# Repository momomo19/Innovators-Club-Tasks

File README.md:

# Innovators Club Tasks

Work from my sessions with Innovators Club, where we're building an energy-efficient
electric car to race in Shell's International Eco-marathon competition. These are some of the
embedded electronics tasks we worked on that built up the skills that we're now using to develop the car's
actual dashboard and GUI pitwall.

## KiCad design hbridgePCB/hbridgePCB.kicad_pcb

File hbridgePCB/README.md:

A single layer H-Bridge PCB I made from scratch.

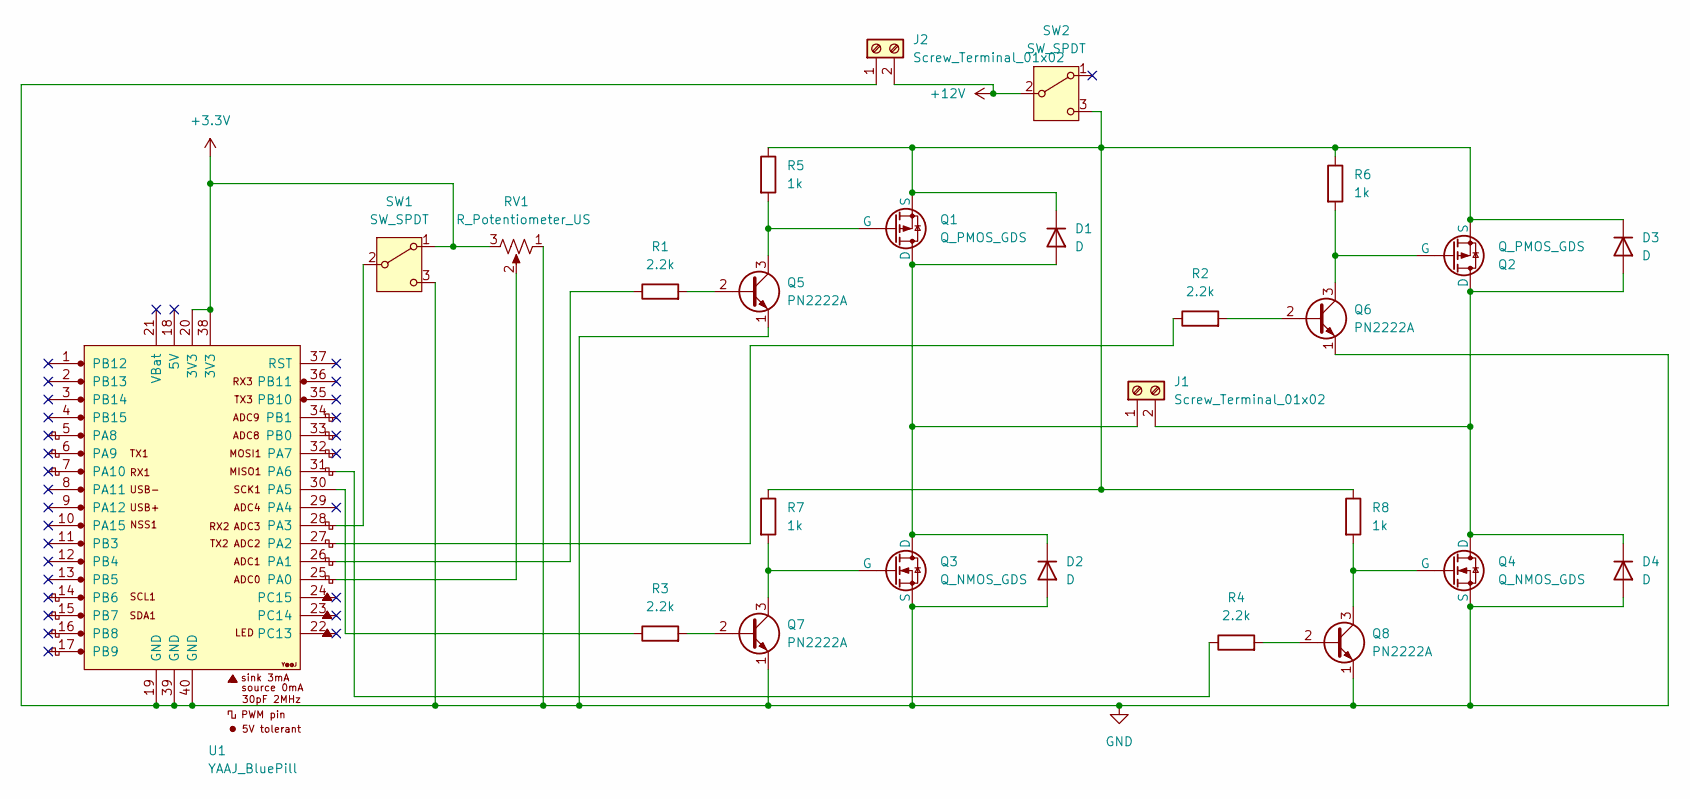
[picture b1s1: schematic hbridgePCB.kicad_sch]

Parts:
D1, D2, D3, D4: D; D_DO-35_SOD27_P10.16mm_Horizontal
J1, J2: Screw_Terminal_01x02; TerminalBlock_MaiXu_MX126-5.0-02P_1x02_P5.00mm
Q1, Q2: Q_PMOS_GDS; TO-220-3_Vertical
Q3, Q4: Q_NMOS_GDS; TO-220-3_Vertical
Q5, Q6, Q7, Q8: PN2222A; TO-92_Wide
R1, R2, R3, R4: 2.2k; R_Axial_DIN0207_L6.3mm_D2.5mm_P10.16mm_Horizontal
R5, R6, R7, R8: 1k; R_Axial_DIN0207_L6.3mm_D2.5mm_P10.16mm_Horizontal
RV1: R_Potentiometer_US; Potentiometer_Piher_PC-16_Single_Horizontal
SW1, SW2: SW_SPDT; SW_Slide-03_Wuerth-WS-SLTV_10x2.5x6.4_P2.54mm
U1: YAAJ_BluePill; YAAJ_BluePill_1

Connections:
+3.3V: RV1.3, SW1.1 (A), U1.20 (3V3), U1.38 (3V3)
+12V: J2.2, SW2.2 (B)
GND: D2.2 (A), D4.2 (A), J2.1, Q3.3 (S), Q4.3 (S), Q5.1 (E), Q6.1 (E), Q7.1 (E), Q8.1 (E), RV1.1, SW1.3 (C), U1.19 (GND), U1.39 (GND), U1.40 (GND)
unnamed: D1.2 (A), D2.1 (K), J1.1, Q1.2 (D), Q3.2 (D)
unnamed: D1.1 (K), D3.1 (K), Q1.3 (S), Q2.3 (S), R5.1, R6.1, R7.1, R8.1, SW2.3 (C)
unnamed: D3.2 (A), D4.1 (K), J1.2, Q2.2 (D), Q4.2 (D)
unnamed: Q1.1 (G), Q5.3 (C), R5.2
unnamed: Q2.1 (G), Q6.3 (C), R6.2
unnamed: Q3.1 (G), Q7.3 (C), R7.2
unnamed: Q4.1 (G), Q8.3 (C), R8.2
unnamed: Q5.2 (B), R1.2
unnamed: Q6.2 (B), R2.2
unnamed: Q7.2 (B), R3.2
unnamed: Q8.2 (B), R4.2
unnamed: SW1.2 (B), U1.28 (PA3)
unnamed: RV1.2, U1.25 (PA0)
unnamed: R1.1, U1.26 (PA1)
unnamed: R2.1, U1.27 (PA2)
unnamed: R3.1, U1.30 (PA5)
unnamed: R4.1, U1.31 (PA6)

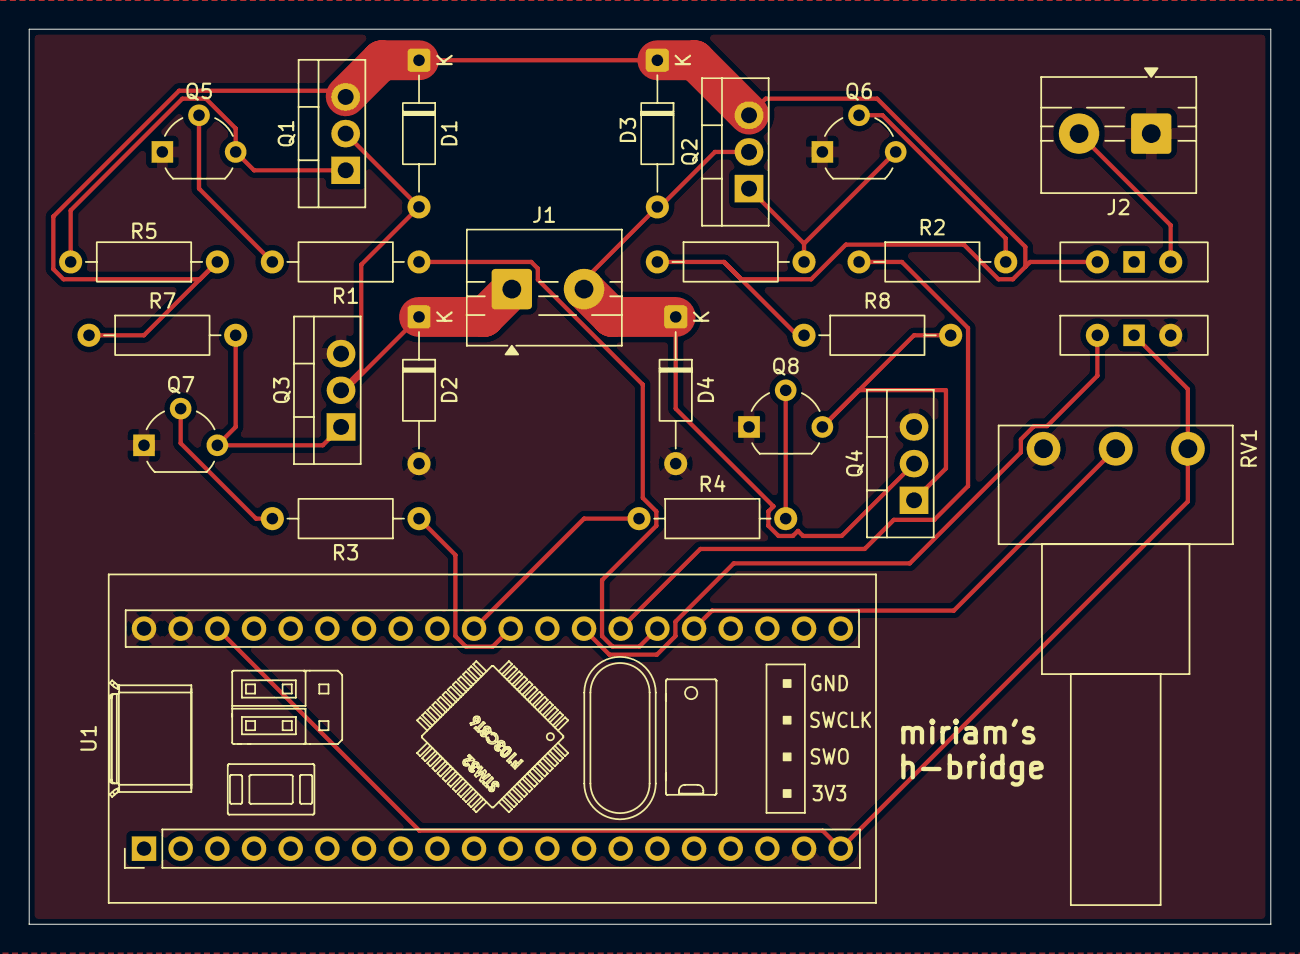
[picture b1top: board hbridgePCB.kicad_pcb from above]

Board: 2 copper layers, 86.0 x 62.0 mm, 26 parts (0 on the bottom side), 20 nets.
